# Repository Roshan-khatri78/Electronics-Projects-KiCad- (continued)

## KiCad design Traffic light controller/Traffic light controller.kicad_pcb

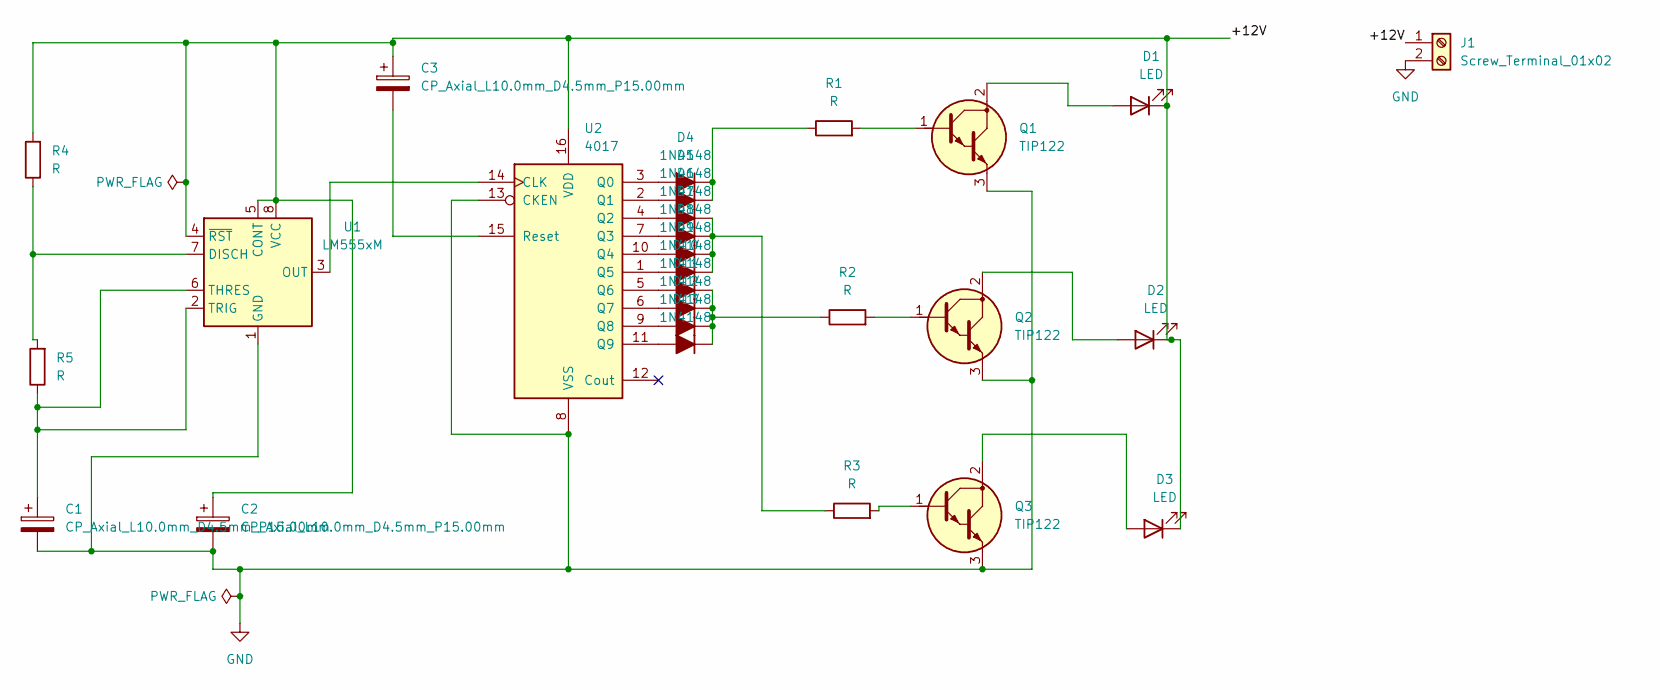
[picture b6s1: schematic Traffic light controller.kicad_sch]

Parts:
C1, C2, C3: CP_Axial_L10.0mm_D4.5mm_P15.00mm; CP_Axial_L10.0mm_D4.5mm_P15.00mm_Horizontal
D1, D2, D3: LED; LED_D5.0mm
D4, D5, D6, D7, D8, D9, D10, D11, D12, D13: 1N4148; D_5W_P12.70mm_Horizontal
J1: Screw_Terminal_01x02; TerminalBlock_MaiXu_MX126-5.0-02P_1x02_P5.00mm
Q1, Q2, Q3: TIP122; TO-220-3_Vertical_BCE
R1, R2, R3, R4, R5: R; R_Axial_DIN0204_L3.6mm_D1.6mm_P1.90mm_Vertical
U1: LM555xM; SOIC-8_3.9x4.9mm_P1.27mm
U2: 4017; DIP-16_W10.16mm

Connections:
/+12V: C2.1, C3.1, D1.1 (K), D2.1 (K), D3.1 (K), J1.1, R4.2, U1.4 (~RST), U1.5 (CONT), U1.8 (VCC), U2.16 (VDD)
GND: C1.2, C2.2, J1.2, Q1.3 (E), Q2.3 (E), Q3.3 (E), U1.1 (GND), U2.8 (VSS), U2.13 (CKEN)
unnamed: D1.2 (A), Q1.2 (C)
unnamed: D2.2 (A), Q2.2 (C)
unnamed: D3.2 (A), Q3.2 (C)
unnamed: D4.2 (A), U2.3 (Q0)
unnamed: D4.1 (K), D5.1 (K), R1.1
unnamed: D5.2 (A), U2.2 (Q1)
unnamed: D6.2 (A), U2.4 (Q2)
unnamed: D6.1 (K), D7.1 (K), D8.1 (K), D9.1 (K), R3.1
unnamed: D7.2 (A), U2.7 (Q3)
unnamed: D8.2 (A), U2.10 (Q4)
unnamed: D9.2 (A), U2.1 (Q5)
unnamed: D10.2 (A), U2.5 (Q6)
unnamed: D10.1 (K), D11.1 (K), D12.1 (K), D13.1 (K), R2.1
unnamed: D11.2 (A), U2.6 (Q7)
unnamed: D12.2 (A), U2.9 (Q8)
unnamed: D13.2 (A), U2.11 (Q9)
unnamed: Q1.1 (B), R1.2
unnamed: Q2.1 (B), R2.2
unnamed: Q3.1 (B), R3.2
unnamed: R4.1, R5.2, U1.7 (DISCH)
unnamed: U1.3 (OUT), U2.14 (CLK)
unnamed: C1.1, R5.1, U1.2 (TRIG), U1.6 (THRES)
unnamed: C3.2, U2.15 (Reset)

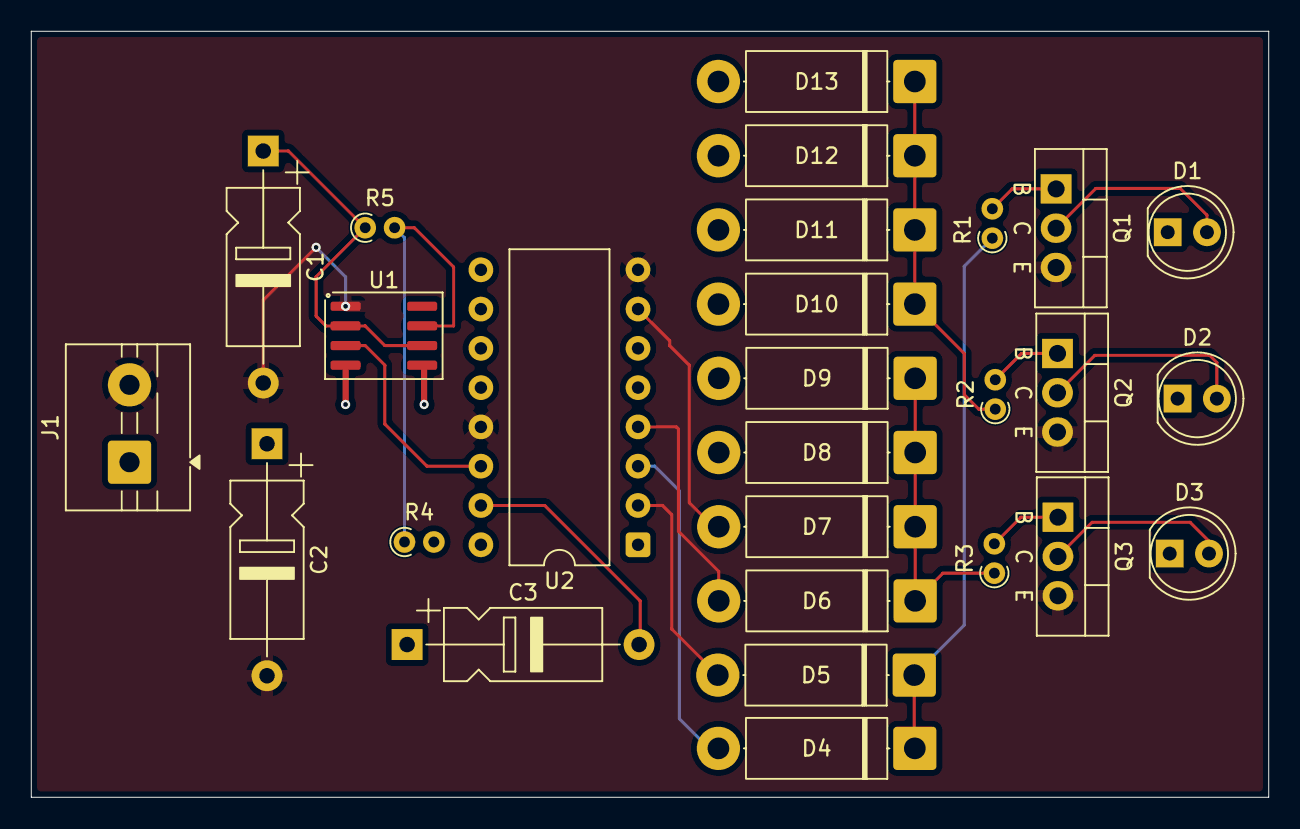
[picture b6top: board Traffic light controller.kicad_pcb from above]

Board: 4 copper layers, 80.0 x 49.5 mm, 27 parts (0 on the bottom side), 25 nets.

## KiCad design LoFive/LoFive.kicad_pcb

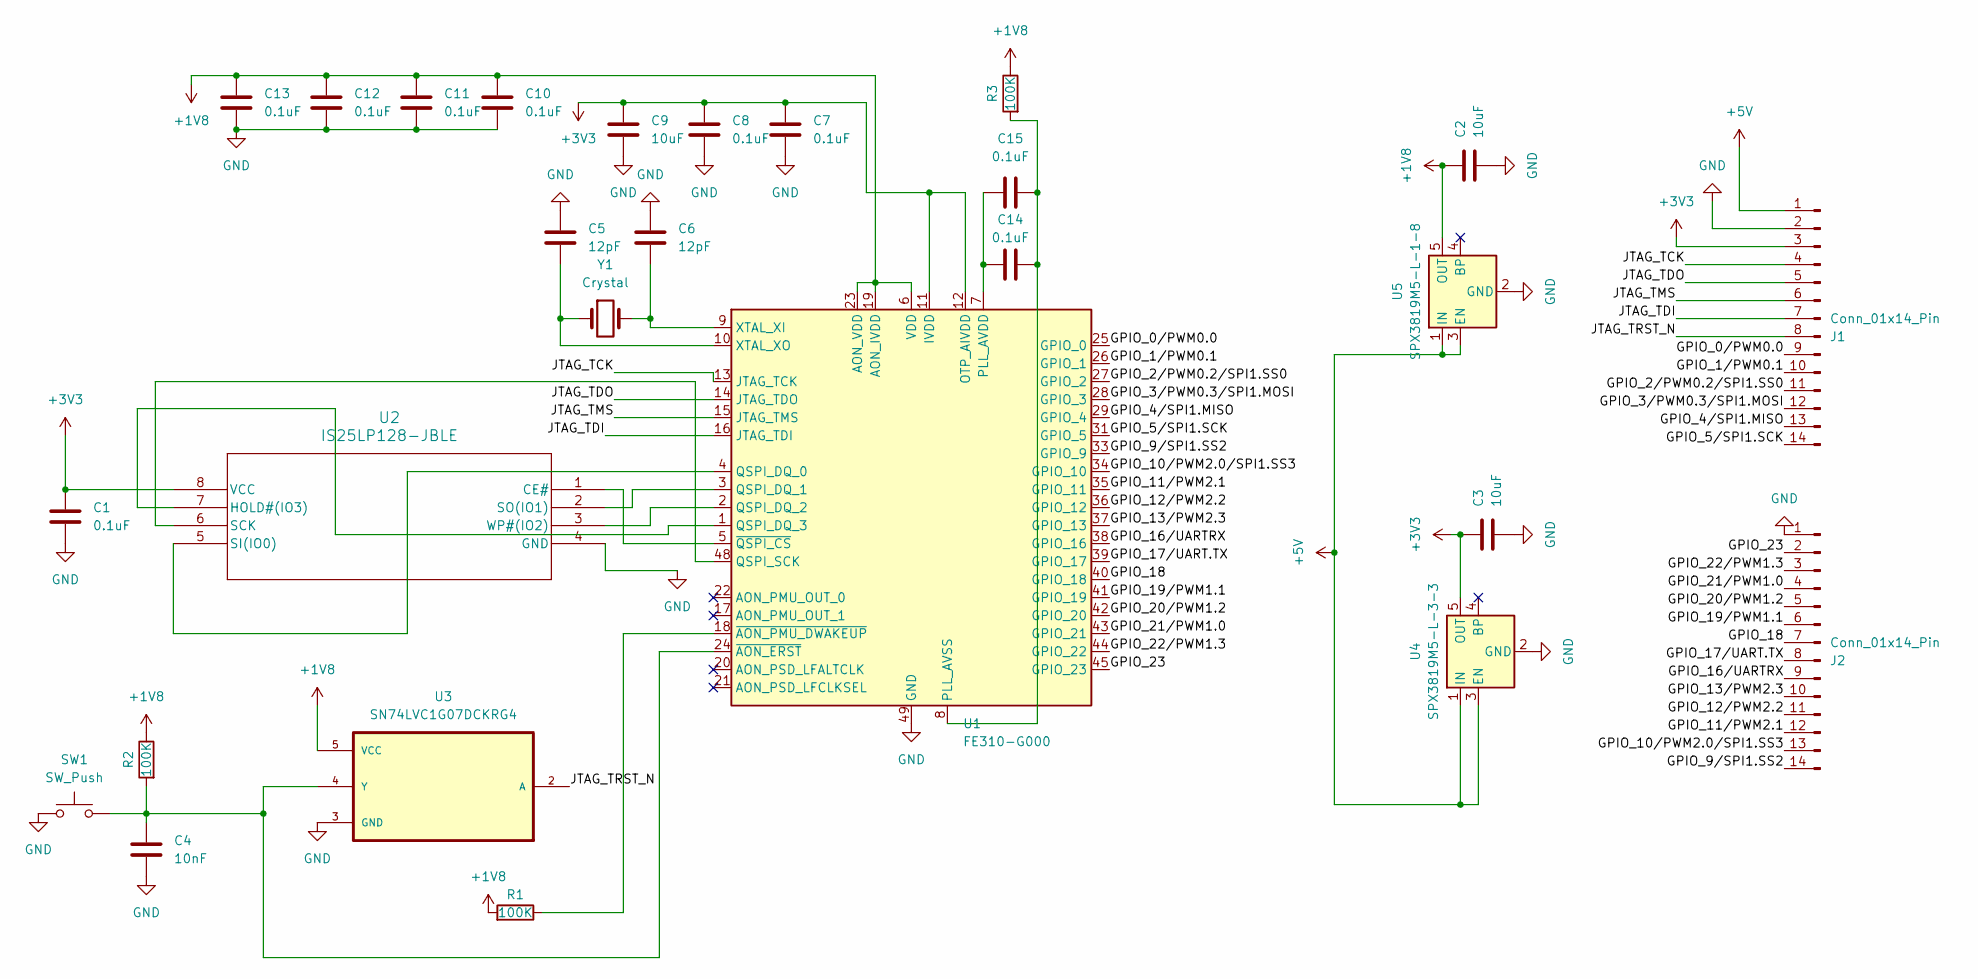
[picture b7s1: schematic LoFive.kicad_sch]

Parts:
C1, C7, C8, C10, C11, C12, C13, C14, C15: 0.1uF; C_0402_1005Metric_Pad0.74x0.62mm_HandSolder
C2, C3, C9: 10uF; C_0402_1005Metric_Pad0.74x0.62mm_HandSolder
C4: 10nF; C_0402_1005Metric_Pad0.74x0.62mm_HandSolder
C5, C6: 12pF; C_0402_1005Metric_Pad0.74x0.62mm_HandSolder
J1, J2: Conn_01x14_Pin; PinHeader_1x14_P2.54mm_Vertical
R1, R2, R3: 100K; R_0402_1005Metric_Pad0.72x0.64mm_HandSolder
SW1: SW_Push; SW_PUSH_6mm_H5mm
U1: FE310-G000; QFN-48-1EP_6x6mm_P0.4mm_EP4.2x4.2mm_ThermalVias
U2: IS25LP128-JBLE; SOIC8_208MIL_JB_ISI-M
U3: SN74LVC1G07DCKRG4; SOT65P210X110-5N
U4: SPX3819M5-L-3-3; SOT-23-5
U5: SPX3819M5-L-1-8; SOT-23-5
Y1: Crystal; Crystal_SMD_HC49-SD

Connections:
+1V8: C2.1, C10.1, C11.1, C12.1, C13.1, R1.1, R2.2, R3.2, U1.6 (VDD), U1.19 (AON_IVDD), U1.23 (AON_VDD), U1.30 (VDD), U1.46 (VDD), U3.5 (VCC), U5.5 (OUT)
+3V3: C1.1, C3.1, C7.1, C8.1, C9.1, J1.3, U1.11 (IVDD), U1.12 (OTP_AIVDD), U1.32 (IVDD), U1.47 (IVDD), U2.8 (VCC), U4.5 (OUT)
+5V: J1.1, U4.1 (IN), U4.3 (EN), U5.1 (IN), U5.3 (EN)
/GPIO_0/PWM0.0: J1.9, U1.25 (GPIO_0)
/GPIO_1/PWM0.1: J1.10, U1.26 (GPIO_1)
/GPIO_2/PWM0.2/SPI1.SS0: J1.11, U1.27 (GPIO_2)
/GPIO_3/PWM0.3/SPI1.MOSI: J1.12, U1.28 (GPIO_3)
/GPIO_4/SPI1.MISO: J1.13, U1.29 (GPIO_4)
/GPIO_5/SPI1.SCK: J1.14, U1.31 (GPIO_5)
/GPIO_9/SPI1.SS2: J2.14, U1.33 (GPIO_9)
/GPIO_10/PWM2.0/SPI1.SS3: J2.13, U1.34 (GPIO_10)
/GPIO_11/PWM2.1: J2.12, U1.35 (GPIO_11)
/GPIO_12/PWM2.2: J2.11, U1.36 (GPIO_12)
/GPIO_13/PWM2.3: J2.10, U1.37 (GPIO_13)
/GPIO_16/UARTRX: J2.9, U1.38 (GPIO_16)
/GPIO_17/UART.TX: J2.8, U1.39 (GPIO_17)
/GPIO_18: J2.7, U1.40 (GPIO_18)
/GPIO_19/PWM1.1: J2.6, U1.41 (GPIO_19)
/GPIO_20/PWM1.2: J2.5, U1.42 (GPIO_20)
/GPIO_21/PWM1.0: J2.4, U1.43 (GPIO_21)
/GPIO_22/PWM1.3: J2.3, U1.44 (GPIO_22)
/GPIO_23: J2.2, U1.45 (GPIO_23)
/JTAG_TCK: J1.4, U1.13 (JTAG_TCK)
/JTAG_TDI: J1.7, U1.16 (JTAG_TDI)
/JTAG_TDO: J1.5, U1.14 (JTAG_TDO)
/JTAG_TMS: J1.6, U1.15 (JTAG_TMS)
/JTAG_TRST_N: J1.8, U3.2 (A)
GND: C1.2, C2.2, C3.2, C4.2, C5.1, C6.1, C7.2, C8.2, C9.2, C10.2, C11.2, C12.2, C13.2, J1.2, J2.1, SW1.1, U1.49 (GND), U2.4 (GND), U3.3 (GND), U4.2 (GND), U5.2 (GND)
unnamed: C14.1, C15.1, U1.7 (PLL_AVDD)
unnamed: C14.2, C15.2, R3.1, U1.8 (PLL_AVSS)
unnamed: U1.4 (QSPI_DQ_0), U2.5 (SI(IO0))
unnamed: U1.3 (QSPI_DQ_1), U2.2 (SO(IO1))
unnamed: U1.2 (QSPI_DQ_2), U2.3 (WP#(IO2))
unnamed: U1.1 (QSPI_DQ_3), U2.7 (HOLD#(IO3))
unnamed: U1.48 (QSPI_SCK), U2.6 (SCK)
unnamed: C6.2, U1.9 (XTAL_XI), Y1.2
unnamed: C5.2, U1.10 (XTAL_XO), Y1.1
unnamed: C4.1, R2.1, SW1.2, U1.24 (~AON_ERST), U3.4 (Y)
unnamed: R1.2, U1.18 (~AON_PMU_DWAKEUP)
unnamed: U1.5 (~QSPI_CS), U2.1 (CE#)

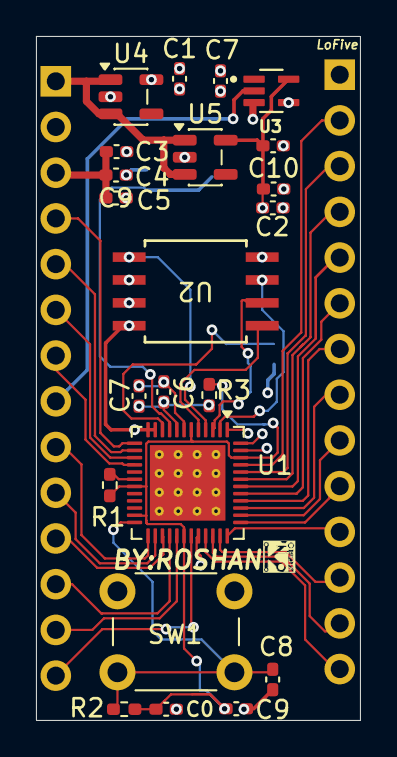
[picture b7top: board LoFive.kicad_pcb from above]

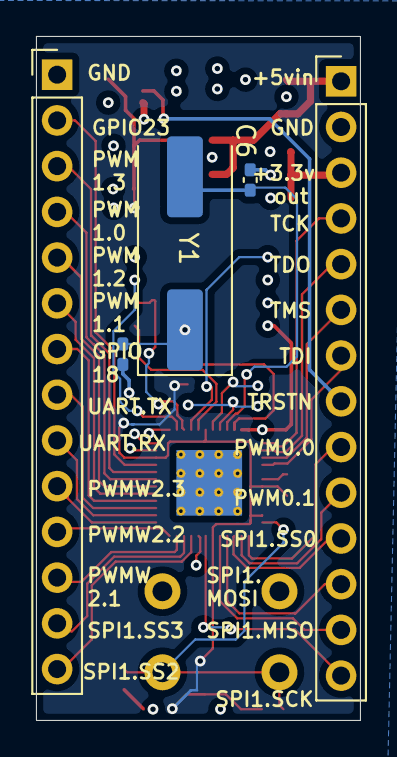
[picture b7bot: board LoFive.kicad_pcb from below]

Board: 4 copper layers, 18.0 x 38.0 mm, 27 parts (5 on the bottom side), 40 nets.

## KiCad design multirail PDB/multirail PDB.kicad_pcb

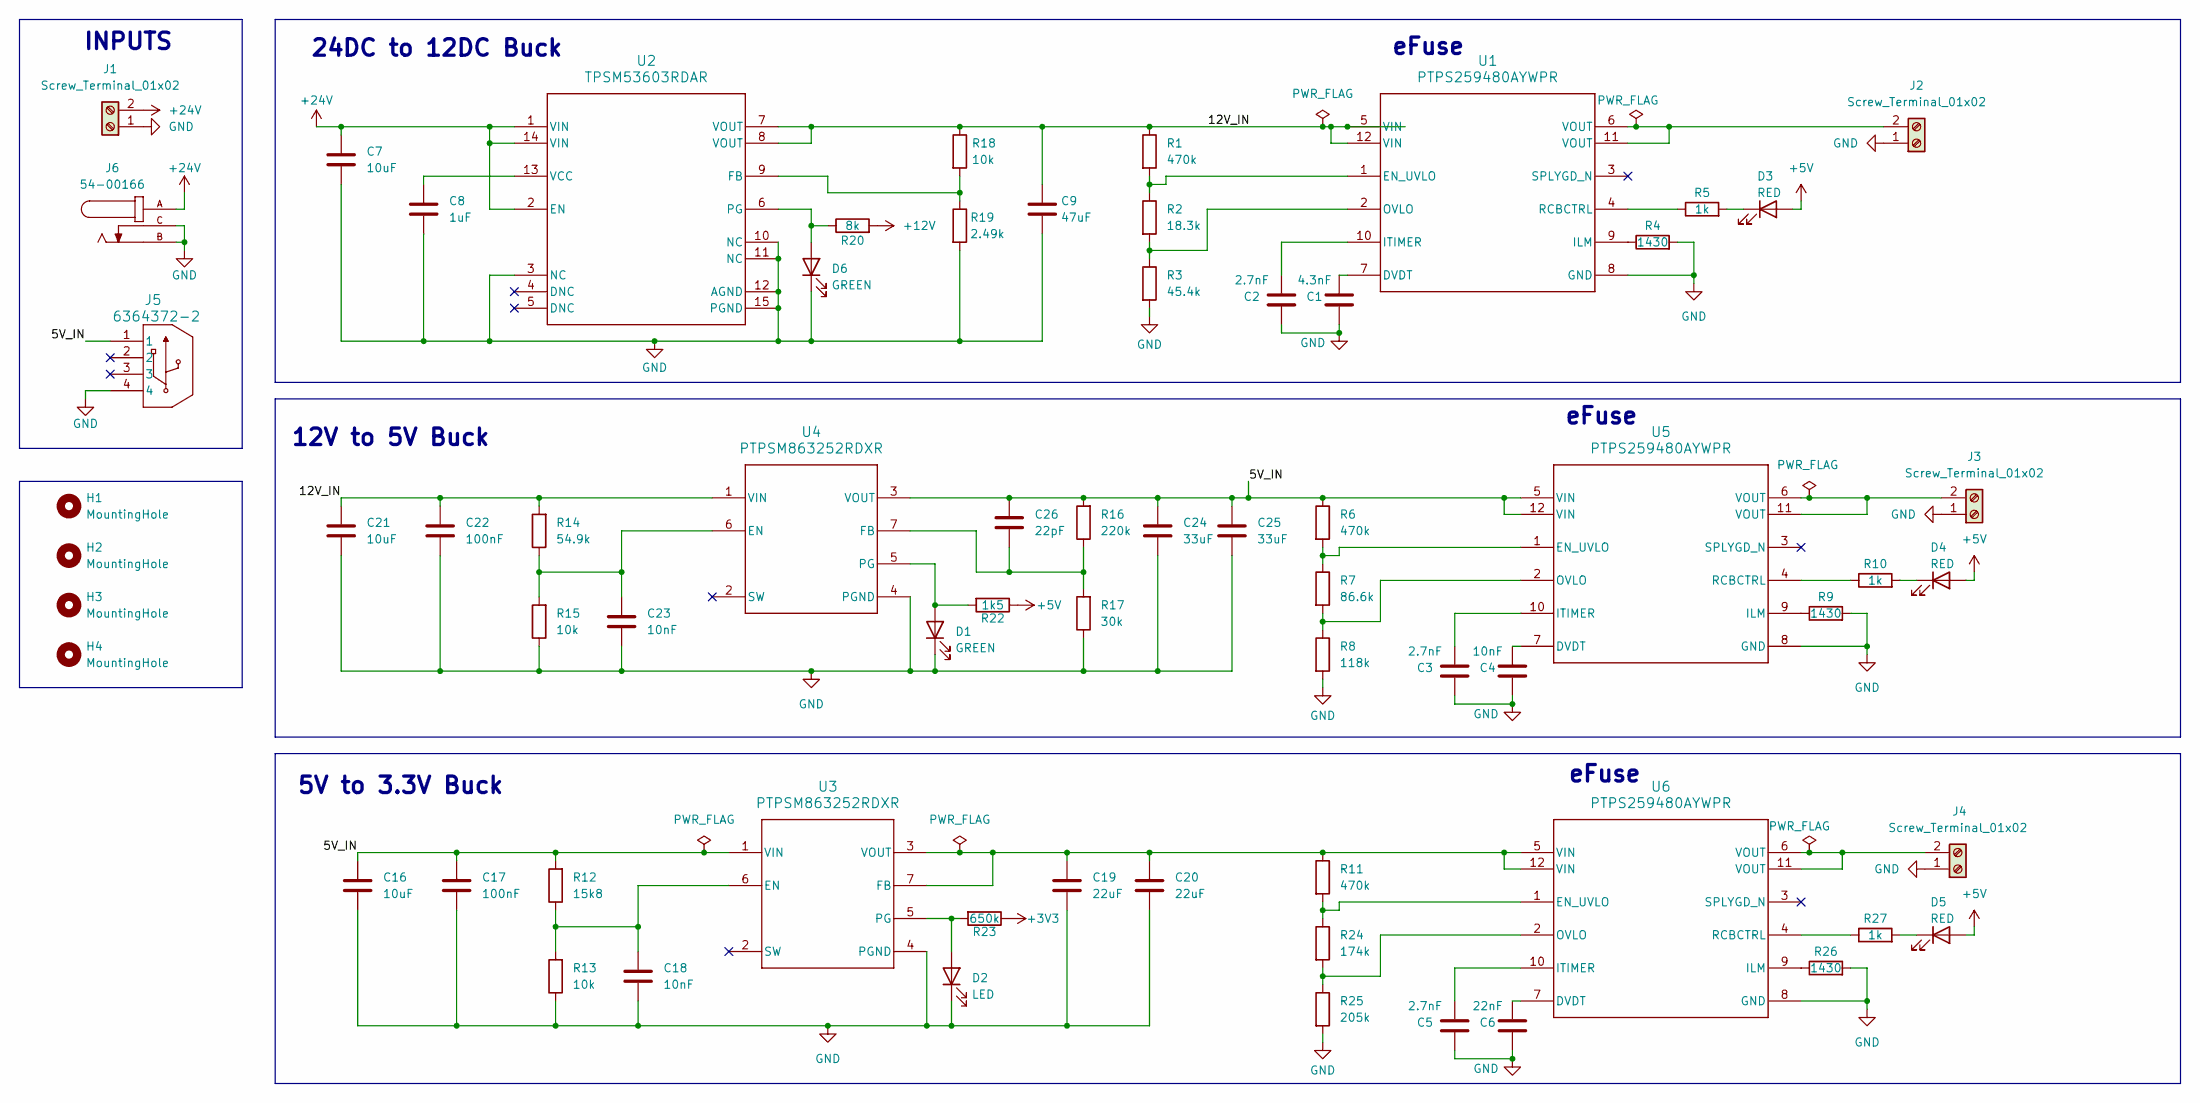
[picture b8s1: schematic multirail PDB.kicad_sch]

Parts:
C1: 4.3nF; C_0805_2012Metric_Pad1.18x1.45mm_HandSolder
C2, C3, C5: 2.7nF; C_0805_2012Metric_Pad1.18x1.45mm_HandSolder
C4: 10nF; C_0805_2012Metric_Pad1.18x1.45mm_HandSolder
C6: 22nF; C_0805_2012Metric_Pad1.18x1.45mm_HandSolder
C7: 10uF; C_0805_2012Metric_Pad1.18x1.45mm_HandSolder
C8: 1uF; C_0805_2012Metric_Pad1.18x1.45mm_HandSolder
C9: 47uF; C_0805_2012Metric_Pad1.18x1.45mm_HandSolder
C16, C21: 10uF; R_0805_2012Metric_Pad1.20x1.40mm_HandSolder
C17, C22: 100nF; R_0805_2012Metric_Pad1.20x1.40mm_HandSolder
C18: 10nF; C_0603_1608Metric_Pad1.08x0.95mm_HandSolder
C19, C20: 22uF; R_0805_2012Metric_Pad1.20x1.40mm_HandSolder
C23: 10nF; R_0603_1608Metric_Pad0.98x0.95mm_HandSolder
C24, C25: 33uF; R_0805_2012Metric_Pad1.20x1.40mm_HandSolder
C26: 22pF; R_0805_2012Metric_Pad1.20x1.40mm_HandSolder
D1, D6: GREEN; LED_0603_1608Metric_Pad1.05x0.95mm_HandSolder
D2: LED; LED_0603_1608Metric_Pad1.05x0.95mm_HandSolder
D3, D4, D5: RED; LED_0603_1608Metric_Pad1.05x0.95mm_HandSolder
H1, H2, H3, H4: MountingHole; MountingHole_3.2mm_M3
J1, J2, J3, J4: Screw_Terminal_01x02; TerminalBlock_Phoenix_PT-1,5-2-5.0-H_1x02_P5.00mm_Horizontal
J5: 6364372-2; USB_A_Connfly_DS1095
J6: 54-00166; TENSILITY_54-00166; PARTREV A
R1, R6, R11: 470k; R_0805_2012Metric_Pad1.20x1.40mm_HandSolder
R2: 18.3k; R_0805_2012Metric_Pad1.20x1.40mm_HandSolder
R3: 45.4k; R_0805_2012Metric_Pad1.20x1.40mm_HandSolder
R4, R9, R26: 1430; R_0805_2012Metric_Pad1.20x1.40mm_HandSolder
R5, R10, R27: 1k; R_0805_2012Metric_Pad1.20x1.40mm_HandSolder
R7: 86.6k; R_0805_2012Metric_Pad1.20x1.40mm_HandSolder
R8: 118k; R_0805_2012Metric_Pad1.20x1.40mm_HandSolder
R12: 15k8; R_0603_1608Metric_Pad0.98x0.95mm_HandSolder
R13, R15: 10k; R_0603_1608Metric_Pad0.98x0.95mm_HandSolder
R14: 54.9k; R_0603_1608Metric_Pad0.98x0.95mm_HandSolder
R16: 220k; R_0603_1608Metric_Pad0.98x0.95mm_HandSolder
R17: 30k; R_0603_1608Metric_Pad0.98x0.95mm_HandSolder
R18: 10k; R_0805_2012Metric_Pad1.20x1.40mm_HandSolder
R19: 2.49k; R_0805_2012Metric_Pad1.20x1.40mm_HandSolder
R20: 8k; R_0805_2012Metric_Pad1.20x1.40mm_HandSolder
R22: 1k5; R_0603_1608Metric_Pad0.98x0.95mm_HandSolder
R23: 650k; R_0603_1608Metric_Pad0.98x0.95mm_HandSolder
R24: 174k; R_0805_2012Metric_Pad1.20x1.40mm_HandSolder
R25: 205k; R_0805_2012Metric_Pad1.20x1.40mm_HandSolder
U1, U5, U6: PTPS259480AYWPR; YWP0012A-MFG
U2: TPSM53603RDAR
U3, U4: PTPSM863252RDXR; RDX0007A-MFG

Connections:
+3V3: R23.1
+5V: D3.2 (A), D4.2 (A), D5.2 (A), R22.1
+12V: R20.2
+24V: C7.1, J1.2, J6.A, U2.1 (VIN), U2.2 (EN), U2.14 (VIN)
/5V_IN: C16.1, C17.1, C24.1, C25.1, C26.1, J5.1, R6.1, R12.2, R16.2, U3.1 (VIN), U4.3 (VOUT), U5.5 (VIN), U5.12 (VIN)
/12V_IN: C9.1, C21.1, C22.1, R1.1, R14.2, R18.1, U1.5 (VIN), U1.12 (VIN), U2.7 (VOUT), U2.8 (VOUT), U4.1 (VIN)
GND: C1.1, C2.1, C3.1, C4.1, C5.1, C6.1, C7.2, C8.2, C9.2, C16.2, C17.2, C18.2, C19.2, C20.2, C21.2, C22.2, C23.2, C24.2, C25.2, D1.1 (K), D2.1 (K), D6.1 (K), J1.1, J2.1, J3.1, J4.1, J5.4, J6.B, J6.C, R3.2, R4.2, R8.2, R9.2, R13.1, R15.1, R17.1, R19.2, R25.2, R26.2, U1.8 (GND), U2.3 (NC), U2.10 (NC), U2.11 (NC), U2.12 (AGND), U2.15 (PGND), U3.4 (PGND), U4.4 (PGND), U5.8 (GND), U6.8 (GND)
unnamed: D1.2 (A), R22.2, U4.5 (PG)
unnamed: D2.2 (A), R23.2, U3.5 (PG)
unnamed: D3.1 (K), R5.2
unnamed: D4.1 (K), R10.2
unnamed: D5.1 (K), R27.2
unnamed: D6.2 (A), R20.1, U2.6 (PG)
unnamed: J2.2, U1.6 (VOUT), U1.11 (VOUT)
unnamed: J3.2, U5.6 (VOUT), U5.11 (VOUT)
unnamed: J4.2, U6.6 (VOUT), U6.11 (VOUT)
unnamed: C1.2, U1.7 (DVDT)
unnamed: R1.2, R2.1, U1.1 (EN_UVLO)
unnamed: R4.1, U1.9 (ILM)
unnamed: C2.2, U1.10 (ITIMER)
unnamed: R2.2, R3.1, U1.2 (OVLO)
unnamed: R5.1, U1.4 (RCBCTRL)
unnamed: R18.2, R19.1, U2.9 (FB)
unnamed: C8.1, U2.13 (VCC)
unnamed: C18.1, R12.1, R13.2, U3.6 (EN)
unnamed: C19.1, C20.1, R11.1, U3.3 (VOUT), U3.7 (FB), U6.5 (VIN), U6.12 (VIN)
unnamed: C23.1, R14.1, R15.2, U4.6 (EN)
unnamed: C26.2, R16.1, R17.2, U4.7 (FB)
unnamed: C4.2, U5.7 (DVDT)
unnamed: R6.2, R7.1, U5.1 (EN_UVLO)
unnamed: R9.1, U5.9 (ILM)
unnamed: C3.2, U5.10 (ITIMER)
unnamed: R7.2, R8.1, U5.2 (OVLO)
unnamed: R10.1, U5.4 (RCBCTRL)
unnamed: C6.2, U6.7 (DVDT)
unnamed: R11.2, R24.1, U6.1 (EN_UVLO)
unnamed: R26.1, U6.9 (ILM)
unnamed: C5.2, U6.10 (ITIMER)
unnamed: R24.2, R25.1, U6.2 (OVLO)
unnamed: R27.1, U6.4 (RCBCTRL)

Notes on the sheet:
24DC to 12DC Buck
5V to 3.3V Buck
INPUTS
12V to 5V Buck
eFuse

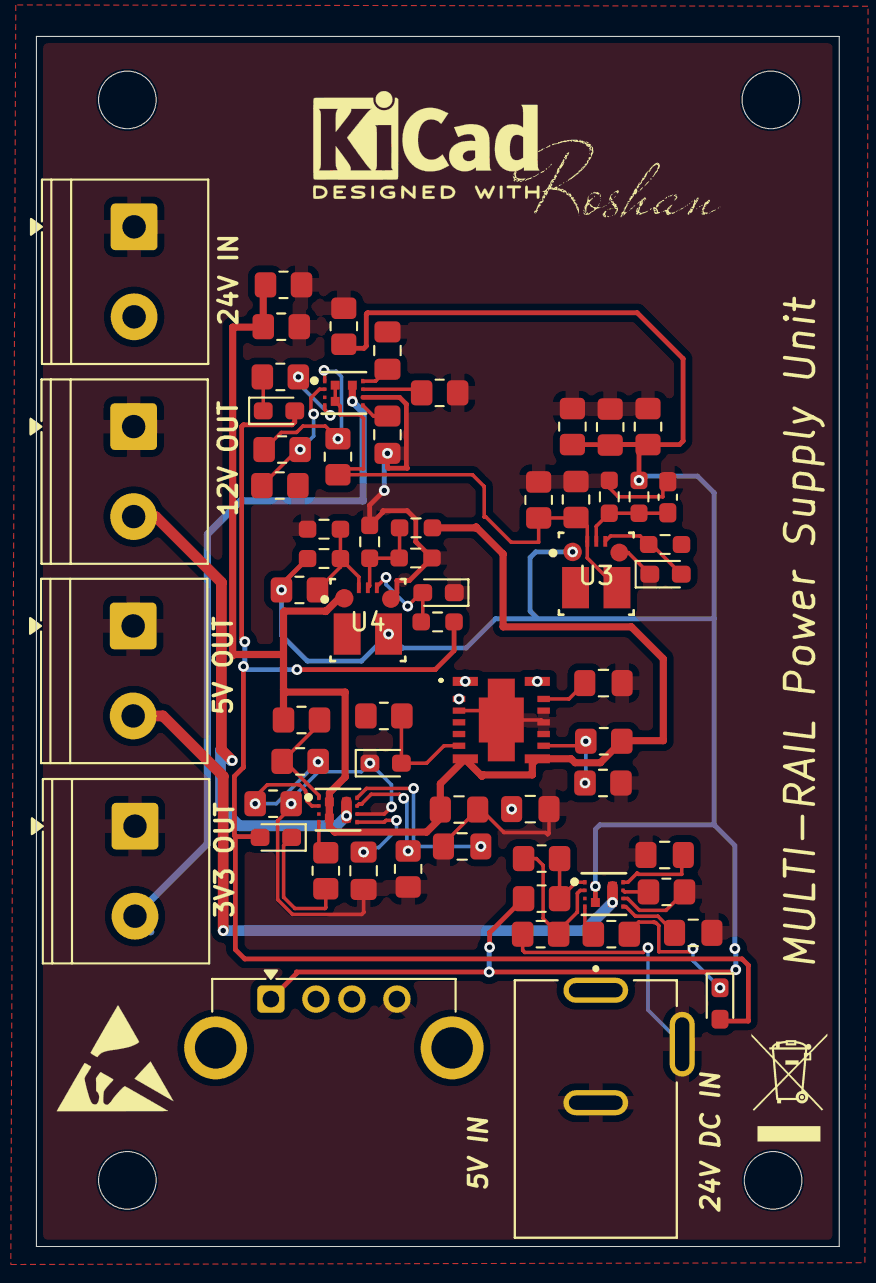
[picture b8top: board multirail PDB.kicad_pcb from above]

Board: 4 copper layers, 44.6 x 67.2 mm, 68 parts (0 on the bottom side), 38 nets.

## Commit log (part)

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2026-06-10 Revise README for KiCad projects portfolio
    Updated README to enhance project description, structure, and goals.
2026-06-10 Add new project files
2026-06-13 Added mini inverter KiCad project
2026-06-16 added smps project
2026-06-16 Revise README with new projects and details
    Updated project descriptions and added new projects including a 60W SMPS and a mini inverter. Enhanced details on key components and concepts for better clarity.
2026-06-16 Fix formatting in README for repository structure section
2026-06-16 Update README with repository structure and tools used
    Added detailed repository structure and project descriptions.
2026-06-17 Added L298 motor pcb
2026-06-23 Added new files
2026-06-28 Update README with new project descriptions and structure
2026-06-28 added new project
